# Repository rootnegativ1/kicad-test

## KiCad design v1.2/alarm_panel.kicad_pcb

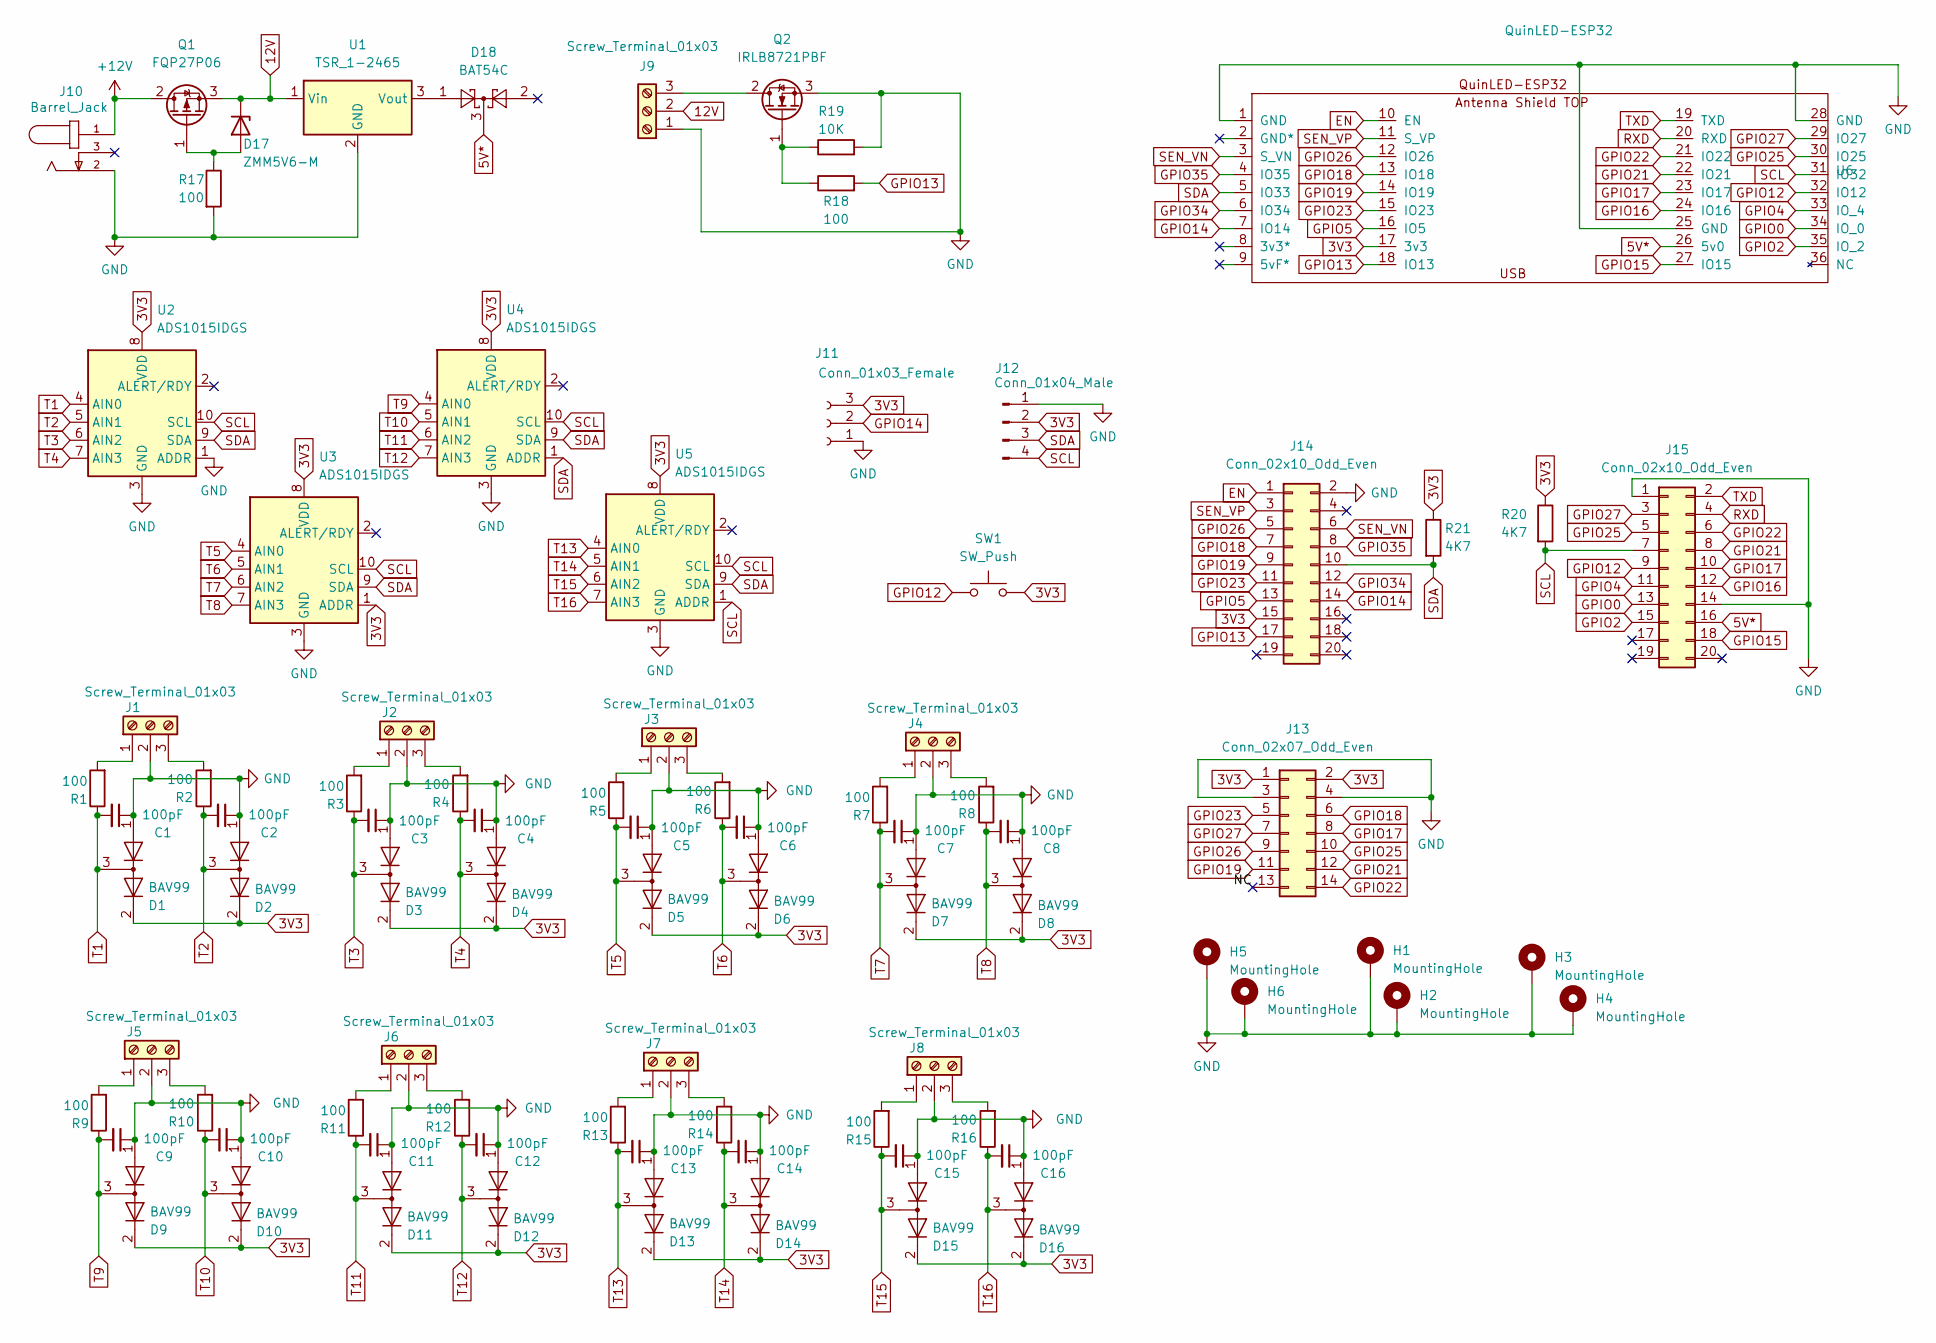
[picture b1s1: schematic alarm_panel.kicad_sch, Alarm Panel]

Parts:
C1, C2, C3, C4, C5, C6, C7, C8, C9, C10, C11, C12, C13, C14, C15, C16: 100pF; C_0805_2012Metric; LCSC C1790
D1, D2, D3, D4, D5, D6, D7, D8, D9, D10, D11, D12, D13, D14, D15, D16: BAV99; SOT-23; LCSC C2500
D17: ZMM5V6-M; D_MiniMELF; LCSC C8062
D18: BAT54C; SOT-23; LCSC C37704
H1, H2, H3, H4: MountingHole; MountingHole_3.2mm_M3_Pad
H5, H6: MountingHole; MountingHole_2.2mm_M2_Pad
J1, J2, J3, J4, J5, J6, J7, J8, J9: Screw_Terminal_01x03; TerminalBlock_Phoenix_PT-1,5-3-5.0-H_1x03_P5.00mm_Horizontal
J10: Barrel_Jack; CUI_PJ-102AH; PART_REV 1.02; LCSC C9900001188
J11: Conn_01x03_Female; PinHeader_1x03_P2.54mm_Vertical
J12: Conn_01x04_Male; JST_PH_B4B-PH-K_1x04_P2.00mm_Vertical; LCSC C131334
J13: Conn_02x07_Odd_Even; PinSocket_2x07_P2.54mm_Vertical
J14, J15: Conn_02x10_Odd_Even; PinSocket_2x10_P2.54mm_Vertical
Q1: FQP27P06; TO-220-3_Vertical; LCSC C462764
Q2: IRLB8721PBF; TO-220-3_Vertical; LCSC C153222
R1, R2, R3, R4, R5, R6, R7, R8, R9, R10, R11, R12, R13, R14, R15, R16, R17, R18: 100; R_0805_2012Metric; LCSC C17408
R19: 10K; R_0805_2012Metric; LCSC C17414
R20, R21: 4K7; R_0805_2012Metric; LCSC C17673
SW1: SW_Push; SW_PUSH_6mm_H4.3mm; LCSC C5143663
U1: TSR_1-2465; Converter_DCDC_TRACO_TSR-1_THT
U2, U3, U4, U5: ADS1015IDGS; TSSOP-10_3x3mm_P0.5mm; LCSC C193969
U6: QuinLED-ESP32

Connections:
5V*: D18.3, J15.16, U6.26 (5v0)
12V: D17.1 (K), J9.2, Q1.3 (S), U1.1 (Vin)
+12V: J10.1, Q1.2 (D)
/NC: J13.13
EN: J14.1, U6.10 (EN)
GPIO0: J15.13, U6.34 (IO_0)
GPIO2: J15.15, U6.35 (IO_2)
GPIO4: J15.11, U6.33 (IO_4)
GPIO5: J14.13, U6.16 (IO5)
GPIO12: J15.9, SW1.1, U6.32 (IO12)
GPIO13: J14.17, R18.2, U6.18 (IO13)
GPIO14: J11.2, J14.14, U6.7 (IO14)
GPIO15: J15.18, U6.27 (IO15)
GPIO16: J15.12, U6.24 (IO16)
GPIO17: J13.8, J15.10, U6.23 (IO17)
GPIO18: J13.6, J14.7, U6.13 (IO18)
GPIO19: J13.11, J14.9, U6.14 (IO19)
GPIO21: J13.12, J15.8, U6.22 (IO21)
GPIO22: J13.14, J15.6, U6.21 (IO22)
GPIO23: J13.5, J14.11, U6.15 (IO23)
GPIO25: J13.10, J15.5, U6.30 (IO25)
GPIO26: J13.9, J14.5, U6.12 (IO26)
GPIO27: J13.7, J15.3, U6.29 (IO27)
GPIO34: J14.12, U6.6 (IO34)
GPIO35: J14.8, U6.4 (IO35)
unnamed: D17.2 (A), Q1.1 (G), R17.1
unnamed: D18.1, U1.3 (Vout)
unnamed: J1.1, R1.2
unnamed: J1.3, R2.2
unnamed: J2.1, R3.2
unnamed: J2.3, R4.2
unnamed: J3.1, R5.2
unnamed: J3.3, R6.2
unnamed: J4.1, R7.2
unnamed: J4.3, R8.2
unnamed: J5.1, R9.2
unnamed: J5.3, R10.2
unnamed: J6.1, R11.2
unnamed: J6.3, R12.2
unnamed: J7.1, R13.2
unnamed: J7.3, R14.2
unnamed: J8.1, R15.2
unnamed: J8.3, R16.2
unnamed: J9.3, Q2.2 (D)
unnamed: Q2.1 (G), R18.1, R19.1
RXD: J15.4, U6.20 (RXD)
SCL: J12.4, J15.7, R20.2, U2.10 (SCL), U3.10 (SCL), U4.10 (SCL), U5.1 (ADDR), U5.10 (SCL), U6.31 (IO32)
SDA: J12.3, J14.10, R21.2, U2.9 (SDA), U3.9 (SDA), U4.1 (ADDR), U4.9 (SDA), U5.9 (SDA), U6.5 (IO33)
SEN_VN: J14.6, U6.3 (S_VN)
SEN_VP: J14.3, U6.11 (S_VP)
T1: C1.2, D1.3 (K), R1.1, U2.4 (AIN0)
T2: C2.2, D2.3 (K), R2.1, U2.5 (AIN1)
T3: C3.2, D3.3 (K), R3.1, U2.6 (AIN2)
T4: C4.2, D4.3 (K), R4.1, U2.7 (AIN3)
T5: C5.2, D5.3 (K), R5.1, U3.4 (AIN0)
T6: C6.2, D6.3 (K), R6.1, U3.5 (AIN1)
T7: C7.2, D7.3 (K), R7.1, U3.6 (AIN2)
T8: C8.2, D8.3 (K), R8.1, U3.7 (AIN3)
T9: C9.2, D9.3 (K), R9.1, U4.4 (AIN0)
T10: C10.2, D10.3 (K), R10.1, U4.5 (AIN1)
T11: C11.2, D11.3 (K), R11.1, U4.6 (AIN2)
T12: C12.2, D12.3 (K), R12.1, U4.7 (AIN3)
T13: C13.2, D13.3 (K), R13.1, U5.4 (AIN0)
T14: C14.2, D14.3 (K), R14.1, U5.5 (AIN1)
T15: C15.2, D15.3 (K), R15.1, U5.6 (AIN2)
T16: C16.2, D16.3 (K), R16.1, U5.7 (AIN3)
TXD: J15.2, U6.19 (TXD)

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
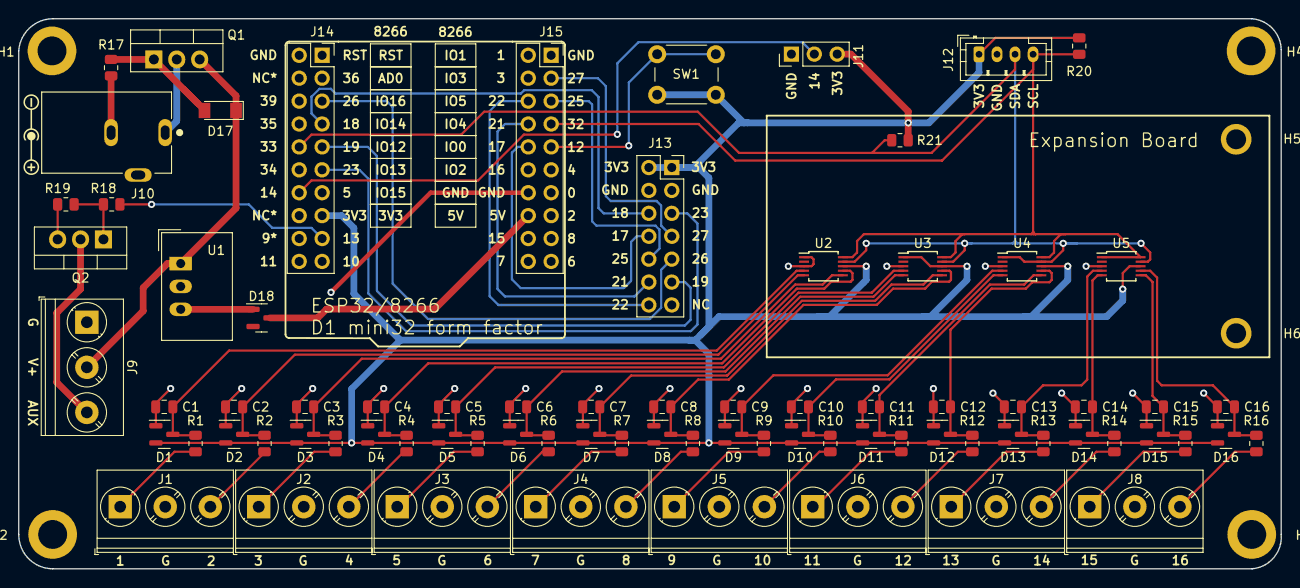
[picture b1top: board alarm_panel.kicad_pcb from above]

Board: 2 copper layers, 140.0 x 61.0 mm, 84 parts (0 on the bottom side), 55 nets.

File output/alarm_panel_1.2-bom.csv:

Row,Description,Part,References,Value,Footprint,Quantity Per PCB,Status,Datasheet,LCSC,JlcRotOffset,PART_REV,STANDARD,MANUFACTURER
1,"Unpolarized capacitor, small symbol",C_Small,C1 C2 C3 C4 C5 C6 C7 C8 C9 C10 C11 C12 C13 C14 C15 C16,100pF,C_0805_2012Metric,16, ,~,C1790,,,,
2,"dual schottky barrier diode, common cathode",BAT54C,D18,BAT54C,SOT-23,1, ,http://www.diodes.com/_files/datasheets/ds11005.pdf,C37704,180,,,
3,"BAV99 High-speed switching diodes, SOT-23",BAV99,D1 D2 D3 D4 D5 D6 D7 D8 D9 D10 D11 D12 D13 D14 D15 D16,BAV99,SOT-23,16, ,~,C2500,180,,,
4,"10V, 500mW, 5%, Zener diode, MiniMELF",BZV55C10,D17,ZMM5V6-M,D_MiniMELF,1, ,,C8062,,,,
5,,PJ-102AH,J10,Barrel_Jack,CUI_PJ-102AH,1, ,https://www.cuidevices.com/product/interconnect/connectors/d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,C9900001188,,1.02,Manufacturer recommendations,CUI INC
6,"Generic connector, single row, 01x03, script generated (kicad-library-utils/schlib/autogen/connector/)",Conn_01x03_Female,J11,Conn_01x03_Female,PinHeader_1x03_P2.54mm_Vertical,1, ,~,,,,,
7,"Generic connector, single row, 01x04, script generated (kicad-library-utils/schlib/autogen/connector/)",Conn_01x04_Male,J12,Conn_01x04_Male,JST_PH_B4B-PH-K_1x04_P2.00mm_Vertical,1, ,https://www.jst-mfg.com/product/pdf/eng/ePH.pdf,C131334,,,,
8,"Generic connector, double row, 02x07, odd/even pin numbering scheme (row 1 odd numbers, row 2 even numbers), script generated (kicad-library-utils/schlib/autogen/connector/)",Conn_02x07_Odd_Even,J13,Conn_02x07_Odd_Even,PinSocket_2x07_P2.54mm_Vertical,1, ,~,,,,,
9,"Generic connector, double row, 02x10, odd/even pin numbering scheme (row 1 odd numbers, row 2 even numbers), script generated (kicad-library-utils/schlib/autogen/connector/)",Conn_02x10_Odd_Even,J14 J15,Conn_02x10_Odd_Even,PinSocket_2x10_P2.54mm_Vertical,2, ,~,,,,,
10,"Generic screw terminal, single row, 01x03, script generated (kicad-library-utils/schlib/autogen/connector/)",Screw_Terminal_01x03,J1 J2 J3 J4 J5 J6 J7 J8 J9,Screw_Terminal_01x03,"TerminalBlock_Phoenix_PT-1,5-3-5.0-H_1x03_P5.00mm_Horizontal",9, ,https://www.phoenixcontact.com/us/products/1935174,,,,,
11,"-27A Id, -60V Vds, QFET P-Channel MOSFET, TO-220",FQP27P06,Q1,FQP27P06,TO-220-3_Vertical,1, ,https://www.onsemi.com/pub/Collateral/FQP27P06-D.PDF,C462764,,,,
12,"62A Id, 30V Vds, 8.7 mOhm Rds, N-Channel HEXFET Power MOSFET, TO-220",IRLB8721PBF,Q2,IRLB8721PBF,TO-220-3_Vertical,1, ,http://www.infineon.com/dgdl/irlb8721pbf.pdf?fileId=5546d462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,C153222,,,,
13,Resistor,R,R1 R2 R3 R4 R5 R6 R7 R8 R9 R10 R11 R12 R13 R14 R15 R16 R17 R18,100,R_0805_2012Metric,18, ,~,C17408,,,,
14,Resistor,R,R20 R21,4K7,R_0805_2012Metric,2, ,~,C17673,,,,
15,Resistor,R,R19,10K,R_0805_2012Metric,1, ,~,C17414,,,,
16,"Push button switch, generic, two pins",SW_Push,SW1,SW_Push,SW_PUSH_6mm_H4.3mm,1, ,~,C5143663,,,,
17,"Ultra-Small, Low-Power, I2C-Compatible, 3.3-kSPS, 12-Bit ADCs With Internal Reference, Oscillator, and Programmable Comparator, VSSOP-10",ADS1015IDGS,U2 U3 U4 U5,ADS1015IDGS,TSSOP-10_3x3mm_P0.5mm,4, ,http://www.ti.com/lit/ds/symlink/ads1015.pdf,C193969,270,,,
18,"1A step-down regulator module, fixed 6.5V output voltage, 9-36V input voltage, -40°C to +85°C temperature range, TO-220 compatible LM78xx replacement",TSR_1-2465,U1,TSR_1-2465,Converter_DCDC_TRACO_TSR-1_THT,1, ,http://www.tracopower.com/products/tsr1.pdf,,,,,

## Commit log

2023-04-23 Rename alarm_panel_v1.2.kicad_pcb to alarm_panel.kicad_pcb
2023-04-23 Rename alarm_panel_v1.2.kicad_sch to alarm_panel.kicad_sch
2023-04-23 Create do-not-delete
2023-04-24 Kicad Action
